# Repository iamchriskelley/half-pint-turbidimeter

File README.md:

#The half-pint turbidimeter
###An awesome water quality monitor about the size of a fist.

Written description coming soon. For now, here's a photo.

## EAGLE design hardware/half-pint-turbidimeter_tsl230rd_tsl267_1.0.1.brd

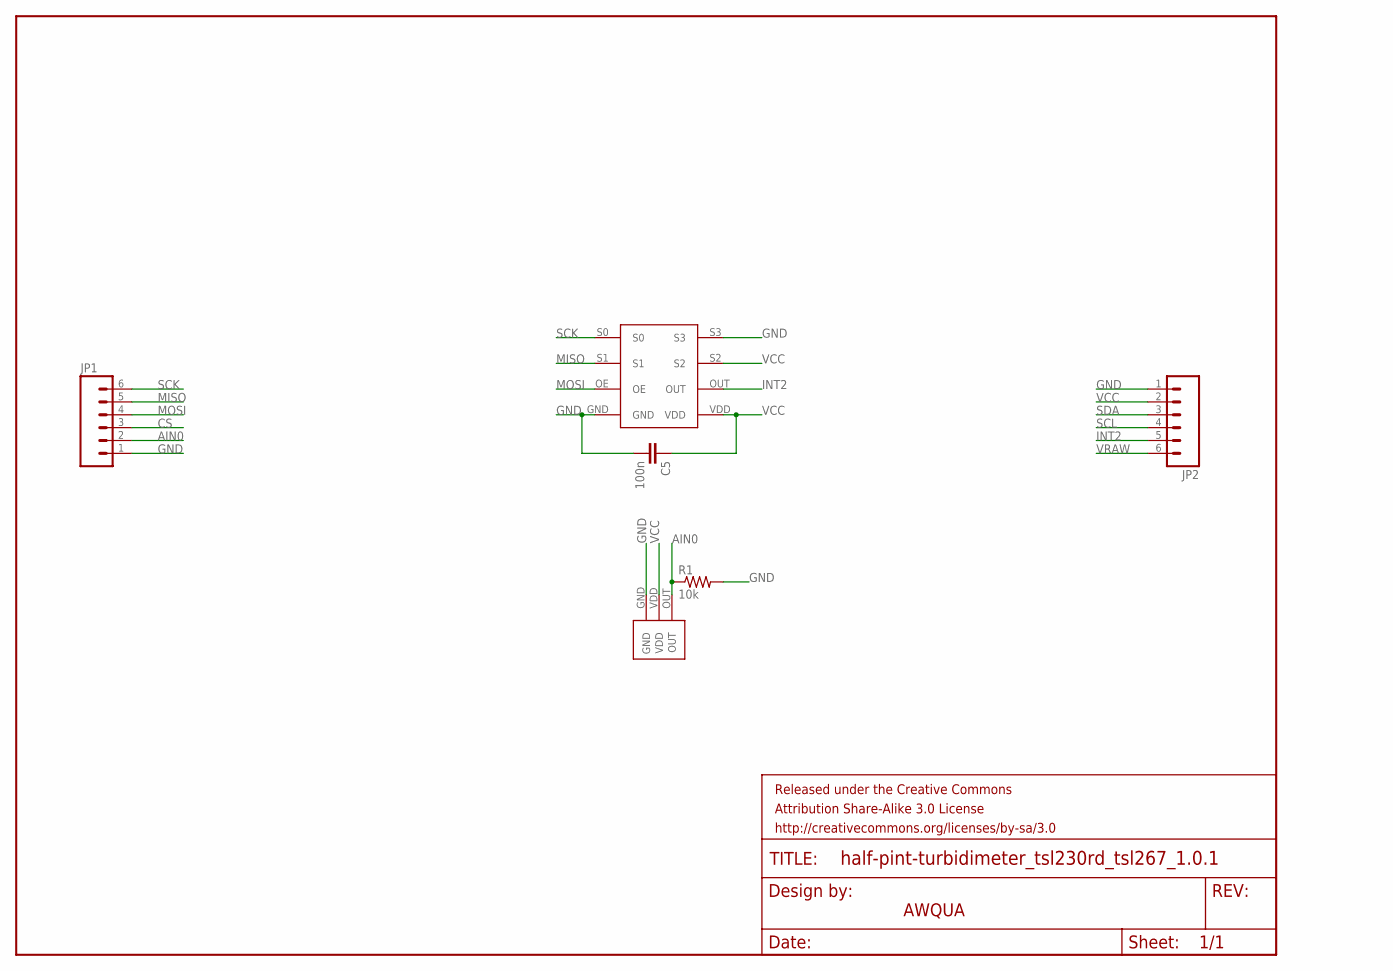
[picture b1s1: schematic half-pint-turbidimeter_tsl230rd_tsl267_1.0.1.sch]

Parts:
C5: 100n; 0603-CAP
FRAME1: FRAME-LETTER; CREATIVE_COMMONS
JP1, JP2: M06SIP; 1X06
R1: 10k; 0603-RES
U$1: TSL267
U$6: TSL230RDSMD; TSL230RD

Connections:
AIN0: JP1.2, R1.1, U$1.OUT
CS: JP1.3
GND: C5.2, JP1.1, JP2.1, R1.2, U$1.GND, U$6.GND, U$6.S3
INT2: JP2.5, U$6.OUT
MISO: JP1.5, U$6.S1
MOSI: JP1.4, U$6.OE
SCK: JP1.6, U$6.S0
SCL: JP2.4
SDA: JP2.3
VCC: C5.1, JP2.2, U$1.VDD, U$6.S2, U$6.VDD
VRAW: JP2.6

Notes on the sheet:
AWQUA

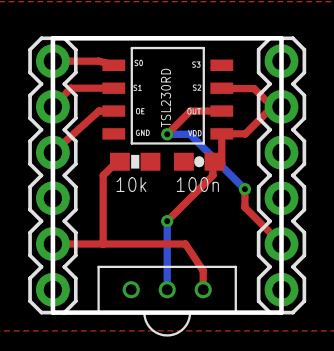
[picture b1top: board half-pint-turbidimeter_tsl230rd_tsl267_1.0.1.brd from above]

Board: 2 copper layers, 12.7 x 15.2 mm, 8 parts (1 on the bottom side), 7 nets.

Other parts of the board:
U$5: OSHW-LOGO-S

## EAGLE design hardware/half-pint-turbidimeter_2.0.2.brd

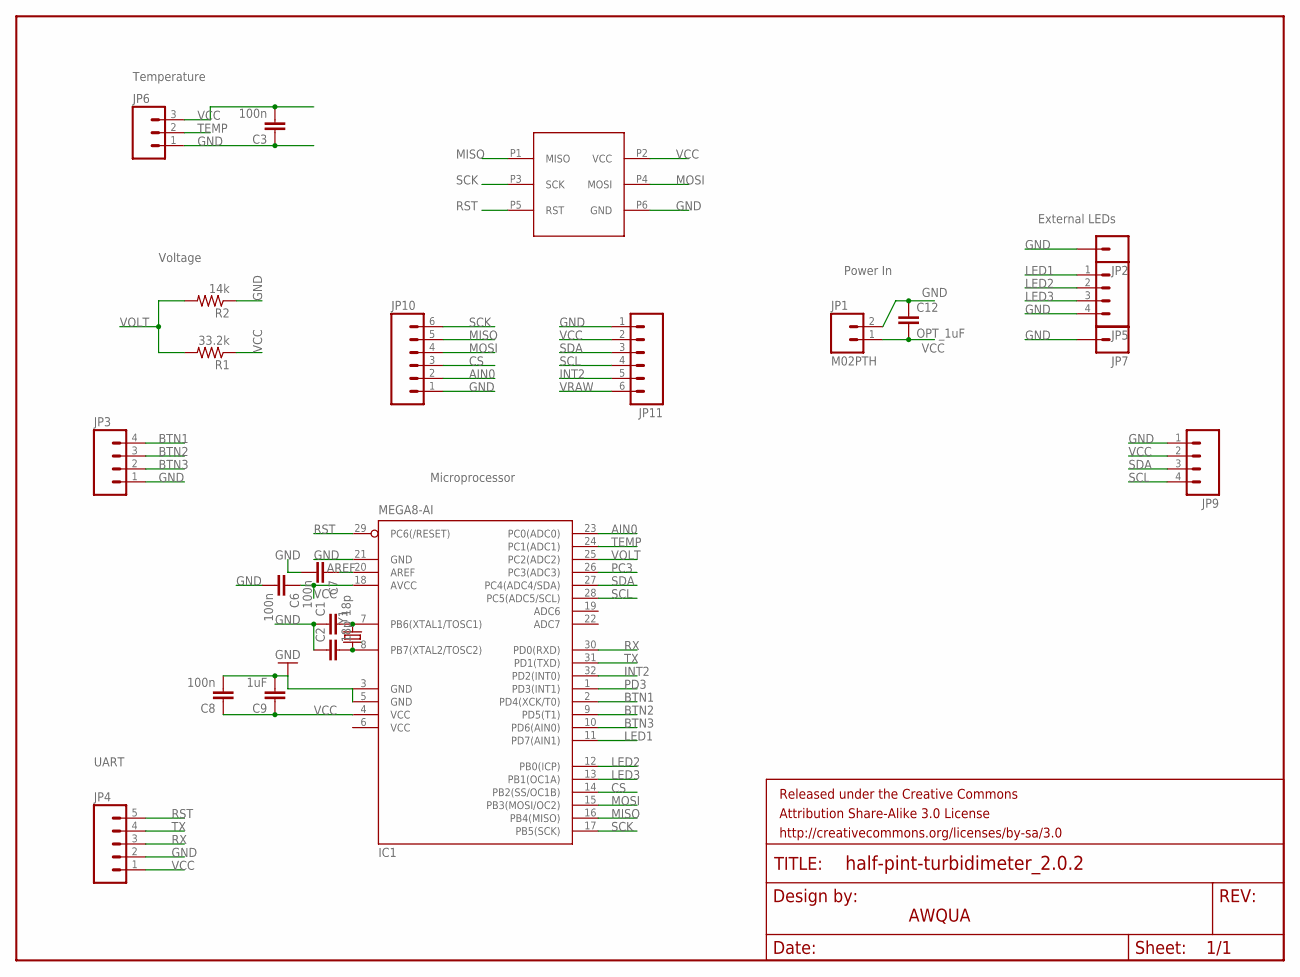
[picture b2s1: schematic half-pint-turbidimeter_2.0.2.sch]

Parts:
C1, C2: 18p; 0603-CAP
C3, C6, C7, C8: 100n; 0603-CAP
C9: 1uF; 0603-CAP
C12: OPT_1uF; 0603-CAP
FRAME1: FRAME-LETTER; CREATIVE_COMMONS
IC1: MEGA8-AI; TQFP32-08
JP1: M02PTH; 1X02
JP2, JP7: M01PTH; 1X01
JP3, JP5, JP9: M04PTH; 1X04
JP4: M05PTH; 1X05
JP6: M03PTH; 1X03
JP10, JP11: M06SMD_MALE; 1X06_SMD_MALE
R1: 33.2k; 0603-RES
R2: 14k; 0603-RES
U$1: ISP-SMD-6PIN
Y1: CRYSTAL5X3; CRYSTAL-SMD-5X3

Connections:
AIN0: IC1.23 (PC0(ADC0)), JP10.2
AREF: C7.1, IC1.20 (AREF)
BTN1: IC1.2 (PD4(XCK/T0)), JP3.4
BTN2: IC1.9 (PD5(T1)), JP3.3
BTN3: IC1.10 (PD6(AIN0)), JP3.2
CS: IC1.14 (PB2(SS/OC1B)), JP10.3
GND: C1.1, C2.1, C3.1, C6.2, C7.2, C8.2, C9.2, C12.1, IC1.3 (GND), IC1.5 (GND), IC1.21 (GND), JP1.2, JP2.1, JP3.1, JP4.2, JP5.4, JP6.1, JP7.1, JP9.1, JP10.1, JP11.1, R2.1, U$1.P6 (GND)
INT2: IC1.32 (PD2(INT0)), JP11.5
LED1: IC1.11 (PD7(AIN1)), JP5.1
LED2: IC1.12 (PB0(ICP)), JP5.2
LED3: IC1.13 (PB1(OC1A)), JP5.3
MISO: IC1.16 (PB4(MISO)), JP10.5, U$1.P1 (MISO)
MOSI: IC1.15 (PB3(MOSI/OC2)), JP10.4, U$1.P4 (MOSI)
PC3: IC1.26 (PC3(ADC3))
PD3: IC1.1 (PD3(INT1))
Q1: C2.2, IC1.8 (PB7(XTAL2/TOSC2)), Y1.1
Q2: C1.2, IC1.7 (PB6(XTAL1/TOSC1)), Y1.3 (2)
RST: IC1.29 (PC6(/RESET)), JP4.5, U$1.P5 (RST)
RX: IC1.30 (PD0(RXD)), JP4.3
SCK: IC1.17 (PB5(SCK)), JP10.6, U$1.P3 (SCK)
SCL: IC1.28 (PC5(ADC5/SCL)), JP9.4, JP11.4
SDA: IC1.27 (PC4(ADC4/SDA)), JP9.3, JP11.3
TEMP: IC1.24 (PC1(ADC1)), JP6.2
TX: IC1.31 (PD1(TXD)), JP4.4
VCC: C3.2, C6.1, C8.1, C9.1, C12.2, IC1.4 (VCC), IC1.6 (VCC), IC1.18 (AVCC), JP1.1, JP4.1, JP6.3, JP9.2, JP11.2, R1.1, U$1.P2 (VCC)
VOLT: IC1.25 (PC2(ADC2)), R1.2, R2.2
VRAW: JP11.6

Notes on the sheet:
AWQUA
Temperature
Voltage
UART
Microprocessor
Power In
External LEDs

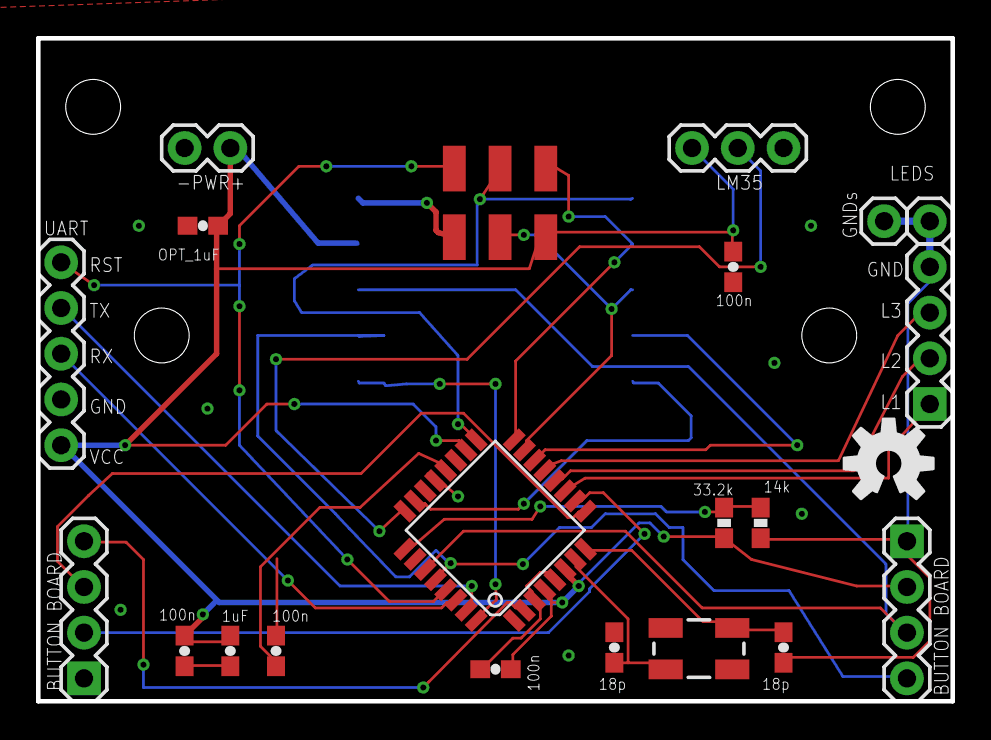
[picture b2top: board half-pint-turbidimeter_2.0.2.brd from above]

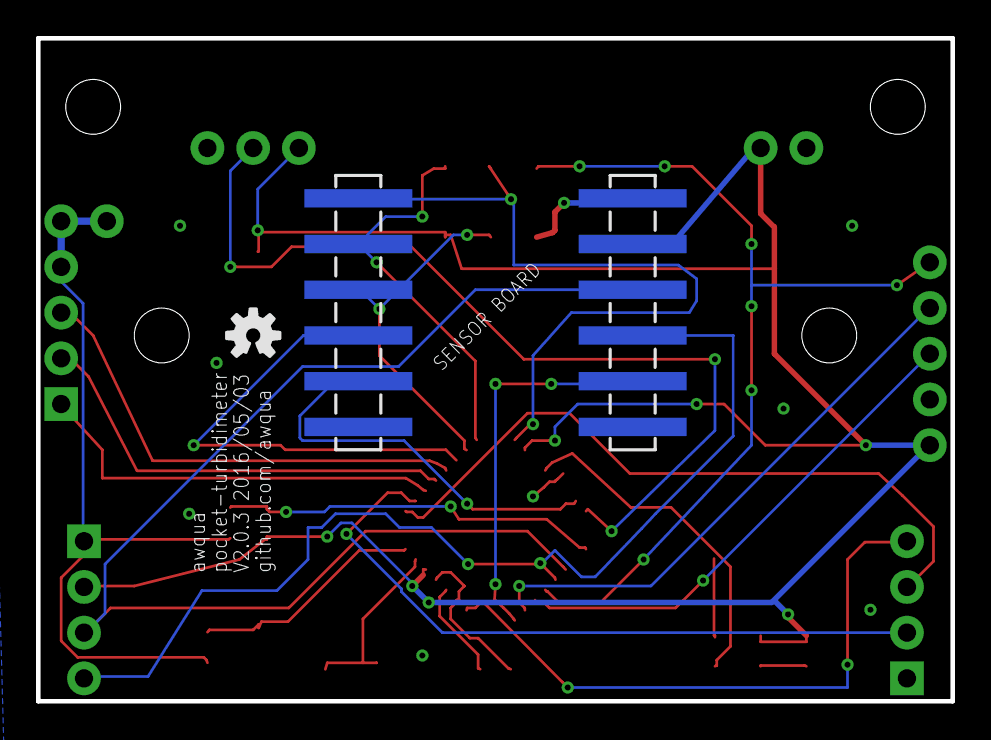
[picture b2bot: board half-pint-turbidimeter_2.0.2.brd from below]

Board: 2 copper layers, 50.8 x 36.8 mm, 26 parts (3 on the bottom side), 24 nets.

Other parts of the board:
U$4: OSHW-LOGO-M
U$5: OSHW-LOGO-S

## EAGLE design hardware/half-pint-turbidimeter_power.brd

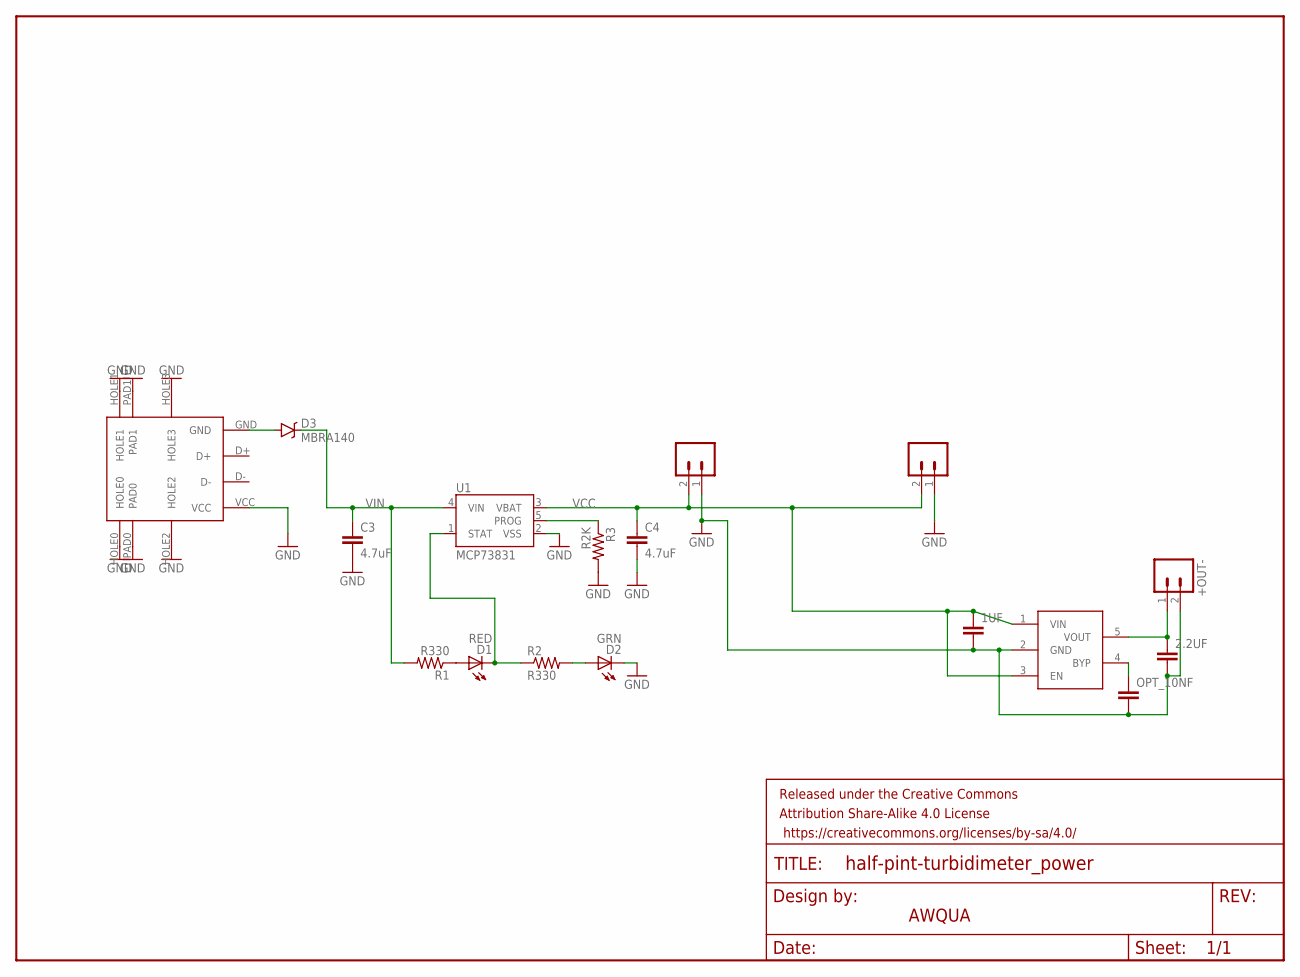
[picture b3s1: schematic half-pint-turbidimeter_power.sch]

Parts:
1UF, 2.2UF: CAP0603-CAP; 0603-CAP
+OUT-: M02PTH; 1X02
C3, C4: 4.7uF; 0402-CAP
D1: RED; LED-0603
D2: GRN; LED-0603
D3: MBRA140; SMA-DIODE
FRAME1: FRAME-LETTER; CREATIVE_COMMONS
JMP: M02PTH; 1X02
JP7: LiPo Battery; JST-2-SMD
OPT_10NF: CAP0603-CAP; 0603-CAP
R1, R2: R330; 0402-RES
R3: R2K; 0402-RES
U1: MCP73831; SOT23-5
U$2: LP2985
U$3: USBMICRO-DX4R005JJ2

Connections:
GND: 1UF.2, 2.2UF.2, +OUT-.2, C3.2, C4.2, D2.C, JMP.1, JP7.1, OPT_10NF.2, R3.2, U1.2 (VSS), U$2.2 (GND), U$3.HOLE0, U$3.HOLE1, U$3.HOLE2, U$3.HOLE3, U$3.PAD0, U$3.PAD1, U$3.VCC
unnamed: OPT_10NF.1, U$2.4 (BYP)
unnamed: D2.A, R2.2
unnamed: D1.A, R1.1
unnamed: 2.2UF.1, +OUT-.1, U$2.5 (VOUT)
unnamed: D3.A, U$3.GND
PROG: R3.1, U1.5 (PROG)
STAT: D1.C, R2.1, U1.1 (STAT)
VCC: 1UF.1, C4.1, JMP.2, JP7.2, U1.3 (VBAT), U$2.1 (VIN), U$2.3 (EN)
VIN: C3.1, D3.C, R1.2, U1.4 (VIN)

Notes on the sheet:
AWQUA

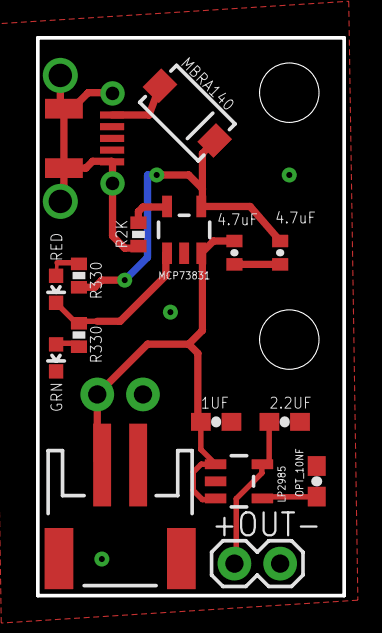
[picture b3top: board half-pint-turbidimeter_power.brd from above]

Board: 2 copper layers, 17.0 x 31.0 mm, 21 parts (1 on the bottom side), 10 nets.

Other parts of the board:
JP1, JP3: STAND-OFF
U$1: CREATIVE_COMMONS

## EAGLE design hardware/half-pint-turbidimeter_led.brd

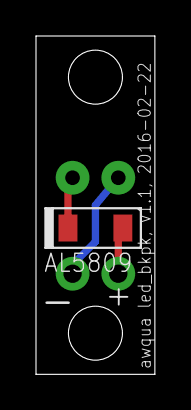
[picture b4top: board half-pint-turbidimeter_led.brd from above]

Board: 2 copper layers, 6.6 x 18.8 mm, 4 parts (1 on the bottom side), 3 nets.

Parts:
D1: LED5MM
JP1: 1X02_NO_SILK
U$1: AL5809
U$2: CREATIVE_COMMONS

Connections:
$N1: D1.A, U$1.OUT
GND: D1.K, JP1.1
VCC: JP1.2, U$1.IN

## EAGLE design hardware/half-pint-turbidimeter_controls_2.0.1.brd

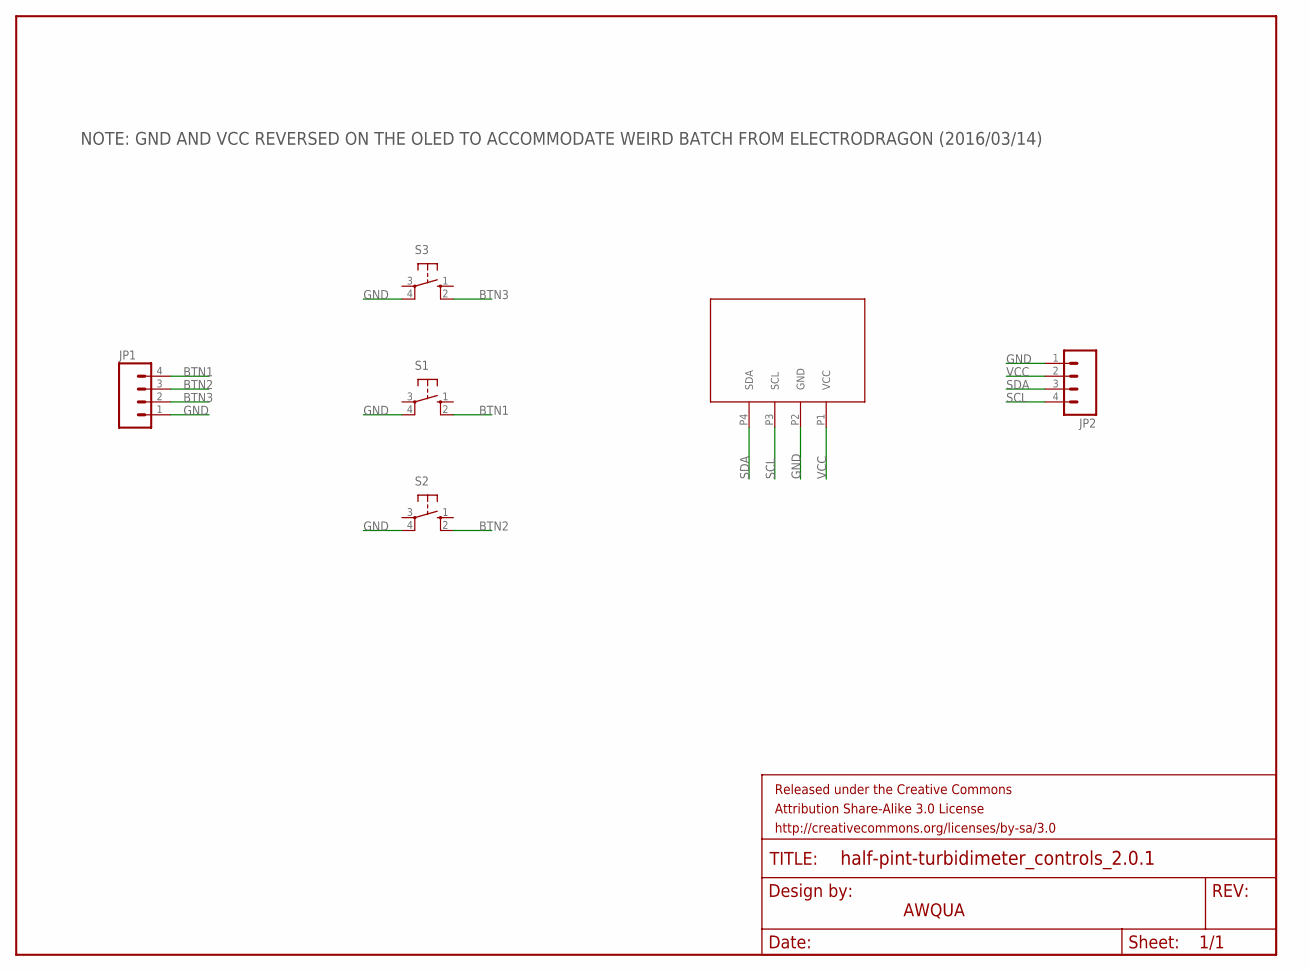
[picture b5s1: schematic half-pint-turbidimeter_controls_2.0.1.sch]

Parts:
FRAME1: FRAME-LETTER; CREATIVE_COMMONS
JP1, JP2: M04PTH; 1X04
S1, S2, S3: 40-XX; B3F-40XX
U$2: I2C-OLED-096

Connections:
BTN1: JP1.4, S1.2 (S1)
BTN2: JP1.3, S2.2 (S1)
BTN3: JP1.2, S3.2 (S1)
GND: JP1.1, JP2.1, S1.4 (P1), S2.4 (P1), S3.4 (P1), U$2.P2 (GND)
SCL: JP2.4, U$2.P3 (SCL)
SDA: JP2.3, U$2.P4 (SDA)
VCC: JP2.2, U$2.P1 (VCC)

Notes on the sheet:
AWQUA
NOTE: GND AND VCC REVERSED ON THE OLED TO ACCOMMODATE WEIRD BATCH FROM ELECTRODRAGON (2016/03/14)

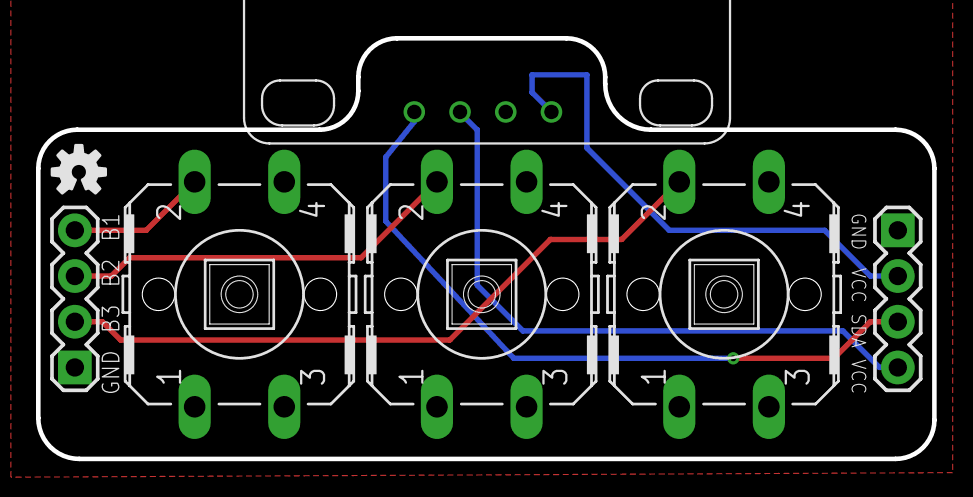
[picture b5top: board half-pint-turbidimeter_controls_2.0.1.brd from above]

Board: 2 copper layers, 49.8 x 23.4 mm, 9 parts (1 on the bottom side), 7 nets.

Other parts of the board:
U$1: OSHW-LOGO-S
U$4: OSHW-LOGO-M

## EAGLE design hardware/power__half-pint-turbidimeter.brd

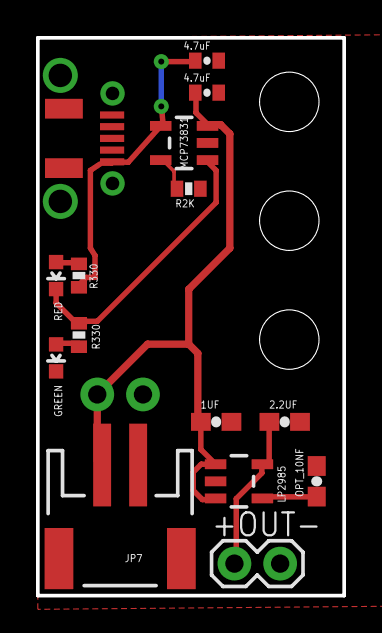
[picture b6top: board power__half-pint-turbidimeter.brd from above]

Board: 2 copper layers, 17.0 x 31.0 mm, 19 parts (1 on the bottom side), 9 nets.

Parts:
1UF, 2.2UF: 0603-CAP
+OUT-: 1X02
C3, C4: 4.7uF; 0402-CAP
D1: GREEN; LED-0603
D11: RED; LED-0603
JMP: 1X02
JP1, JP2, JP3: STAND-OFF
JP7: LiPo Battery; JST-2-SMD
OPT_10NF: 0603-CAP
R1: R330; 0402-RES
R2K: 2K; 0402-RES
R330: 330; 0402-RES
U1: MCP73831; SOT23-5
U$2: LP2985
U$3: USBMICRO-DX4R005JJ2

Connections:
GND: 1UF.2, 2.2UF.2, +OUT-.2, C3.2, C4.2, D1.C, JMP.1, JP7.1, OPT_10NF.2, R2K.2, U1.2, U$2.2, U$3.GND, U$3.HOLE0, U$3.HOLE1, U$3.HOLE2, U$3.HOLE3, U$3.PAD0, U$3.PAD1
unnamed: OPT_10NF.1, U$2.4
unnamed: D1.A, R1.2
unnamed: D11.A, R330.1
unnamed: 2.2UF.1, +OUT-.1, U$2.5
PROG: R2K.1, U1.5
STAT: D11.C, R1.1, U1.1
VCC: 1UF.1, C4.1, JMP.2, JP7.2, U1.3, U$2.1, U$2.3
VIN: C3.1, R330.2, U1.4, U$3.VCC

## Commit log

2016-03-29 imported main, interface boards
2016-03-30 next version started
2016-03-30 updating v2.0.2
2016-03-31 minor edits to eagle schematics
2016-04-01 airwire fixed
2016-04-01 fixed a label, added smd icsp
2016-04-05 added helper board for led wires
2016-04-07 added voltage protection diode
2016-04-12 added draft of revised caseware
2016-04-19 minor edits
2016-04-19 label edits
2017-01-15 hardware updates

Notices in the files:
parts and their libraries:
SparkFun-Connectors: Licensing: CC v3.0 Share-Alike You are welcome to use this library for commercial purposes.
SparkFun-Aesthetics: Released under the Creative Commons Attribution Share-Alike 3.0 License
SparkFun-Aesthetics: http://creativecommons.org/licenses/by-sa/3.0
